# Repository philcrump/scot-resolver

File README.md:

# scot-resolver

Resolver Interface for the SCOT.

* 22-32V DC Input
* STM32F042K6 Microcontroller @ 48MHz
* MCP2562 CAN 2.0A/B Communication Interface
* AD2S1210 Resolver to Digital Converter
* AD8397 Excitation Driver
* AD8692 Receiver Amplifiers

[**Circuit Board Schematic**](https://github.com/philcrump/scot-resolver/raw/master/scot-resolver-schematic.pdf)

## PCB (CAD Render)

### June 2020 PCB Errata

* C25 has 0603 pad, C27 & C28 have 1210 pads, all should be 0805 to match the part.
* C26 has 1210 pad, should be 1206.
** Not disastrous, part still fits, with careful placement on 1210 to ensure direct contact with the pads.
* Input Voltage rating is 22-32V, not 19-36V as printed on the PCB (limited by U6-LM317 dropout and thermal).
* Optional Ripple Rejection Capacitor should be fitted across R22 (LM317 regulator)
** 2u2 50V found to prevent oscillation with hostile downstream load (oscillating U2-LT1763)
* C24 U2-LT1763 Bypass Capacitor is incorrectly placed, causes self-oscillation, and should not be populated.
** Attempt to wire this across to Vout instead as recommended also caused output oscillation when under load (25mA).
* U6-LM317 regulator gets hot, within limits but would benefit from more heatsinking / different package.

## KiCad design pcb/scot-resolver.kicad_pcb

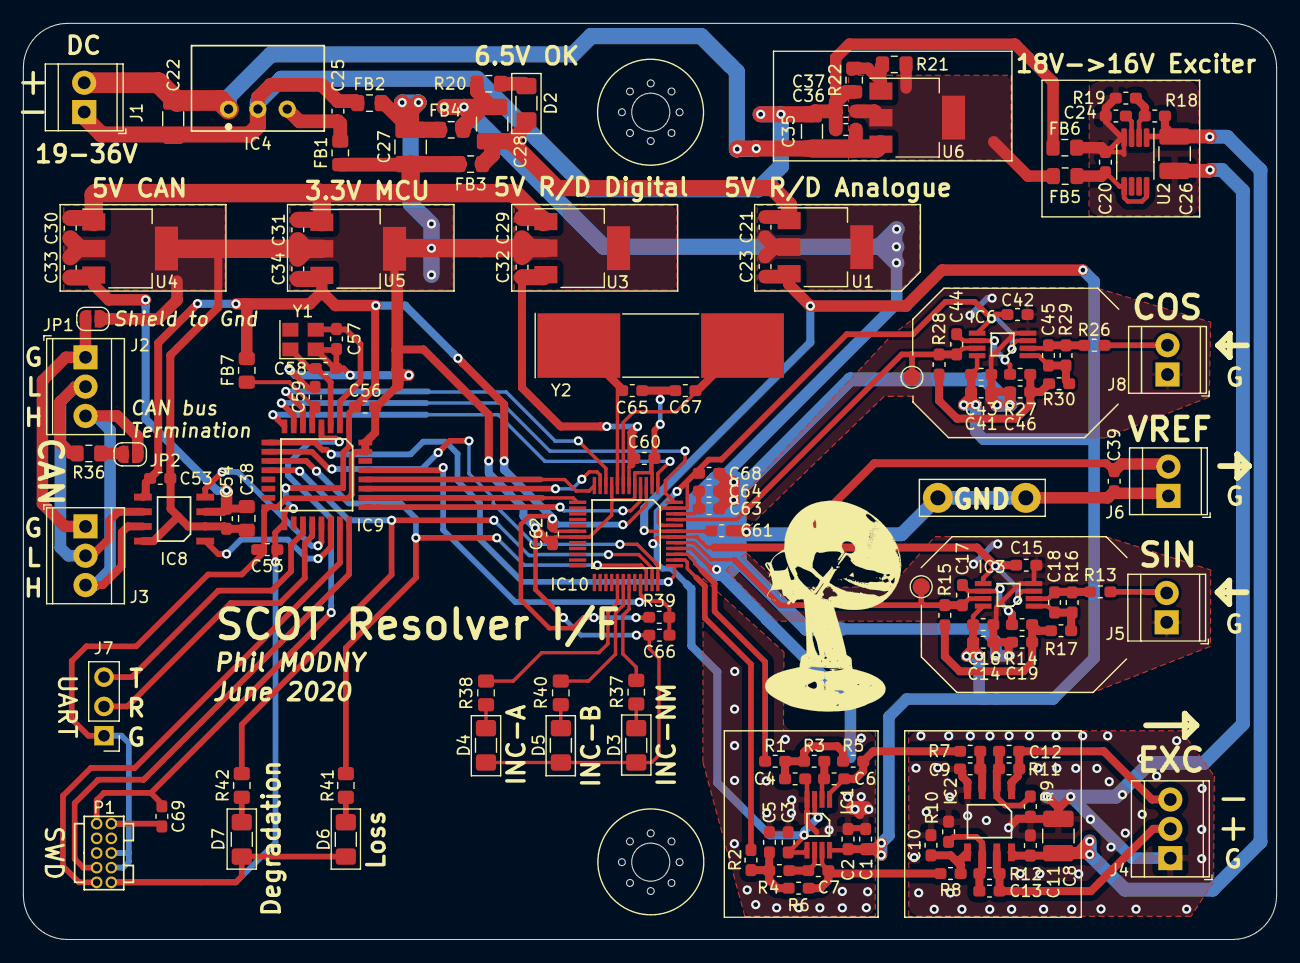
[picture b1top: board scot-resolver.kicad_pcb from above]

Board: 2 copper layers, 108.6 x 79.4 mm, 141 parts (0 on the bottom side), 83 nets.

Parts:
C1, C39, C64: 10u; C_0603_1608Metric_Pad1.05x0.95mm_HandSolder
C2, C3, C11, C15, C16, C42, C43, C55, C56, C59, C60, C61, C62, C66, C68, C69: 100n; C_0603_1608Metric_Pad1.05x0.95mm_HandSolder
C4, C5: 1n; C_0603_1608Metric_Pad1.05x0.95mm_HandSolder
C6, C7: 100p; C_0603_1608Metric_Pad1.05x0.95mm_HandSolder
C8: 10u; C_1210_3225Metric_Pad1.42x2.65mm_HandSolder
C9, C10, C12, C13: 4n7; C_0603_1608Metric_Pad1.05x0.95mm_HandSolder
C14, C20, C41: 1u; C_0603_1608Metric_Pad1.05x0.95mm_HandSolder
C17, C44: 1n2; C_0603_1608Metric_Pad1.05x0.95mm_HandSolder
C18, C45: 220p; C_0603_1608Metric_Pad1.05x0.95mm_HandSolder
C19, C46: 6n8; C_0603_1608Metric_Pad1.05x0.95mm_HandSolder
C21, C29, C30, C31: 1u/6.5V; C_0603_1608Metric_Pad1.05x0.95mm_HandSolder
C22, C35: 4u7/50V; C_1206_3216Metric_Pad1.42x1.75mm_HandSolder
C23, C32, C33: 1u/5V; C_0603_1608Metric_Pad1.05x0.95mm_HandSolder
C24: 10n/50V; C_0603_1608Metric_Pad1.05x0.95mm_HandSolder
C25: 4u7/6.5V; C_0603_1608Metric_Pad1.05x0.95mm_HandSolder
C26: 4u7/50V; C_1210_3225Metric_Pad1.42x2.65mm_HandSolder
C27, C28: 4u7/6.5V; C_1210_3225Metric_Pad1.42x2.65mm_HandSolder
C34: 1u/3.3V; C_0603_1608Metric_Pad1.05x0.95mm_HandSolder
C36: 100n/50V; C_0603_1608Metric_Pad1.05x0.95mm_HandSolder
C37: 4u7/50V; C_0603_1608Metric_Pad1.05x0.95mm_HandSolder
C38: 4u7/5V; C_0805_2012Metric_Pad1.15x1.40mm_HandSolder
C53: 100n/3V3; C_0603_1608Metric_Pad1.05x0.95mm_HandSolder
C54: 100n/5V; C_0603_1608Metric_Pad1.05x0.95mm_HandSolder
C57, C58: 8p; C_0603_1608Metric_Pad1.05x0.95mm_HandSolder
C63: 10n; C_0603_1608Metric_Pad1.05x0.95mm_HandSolder
C65, C67: 18p; C_0603_1608Metric_Pad1.05x0.95mm_HandSolder
D2, D3, D4, D5, D6, D7: LED; C_1206_3216Metric_Pad1.42x1.75mm_HandSolder
FB1, FB2, FB3, FB4, FB5, FB6: 600R@100M/1A; L_0805_2012Metric_Pad1.15x1.40mm_HandSolder
FB7: Ferrite_Bead_Small; L_0805_2012Metric_Pad1.15x1.40mm_HandSolder
H1, H2: MountingHole; M3_MOUNT
IC1, IC3, IC6: AD8692ARMZ; MSOP-8
IC2: AD8397ARZ; SOIC-8
IC4: TSR1
IC8: MCP2562; SOIC-8
IC9: STM32F0xxKxTx; LQFP-32
IC10: AD2S1210; LQFP-48
J1, J5, J6, J8: Conn_01x02_Female; TerminalBlock_TE_282834-2_1x02_P2.54mm_Horizontal
J2, J3, J4: Conn_01x03_Female; TerminalBlock_TE_282834-3_1x03_P2.54mm_Horizontal
J7: CONN_01x03; PinHeader_1x03_P2.54mm_Vertical
JP1, JP2: SolderJumper_2_Open; SolderJumper-2_P1.3mm_Open_RoundedPad1.0x1.5mm
P1: SWD; FTSH-105-01-F-D-K
R1, R2, R5, R6: 20k; R_0603_1608Metric_Pad1.05x0.95mm_HandSolder
R3, R4: 6k2; R_0603_1608Metric_Pad1.05x0.95mm_HandSolder
R7, R8: 820R; R_0603_1608Metric_Pad1.05x0.95mm_HandSolder
R9, R10: 390R; R_0603_1608Metric_Pad1.05x0.95mm_HandSolder
R11, R12: 910R; R_0603_1608Metric_Pad1.05x0.95mm_HandSolder
R13, R26: 120K; R_0603_1608Metric_Pad1.05x0.95mm_HandSolder
R14, R27: 1K2; R_0603_1608Metric_Pad1.05x0.95mm_HandSolder
R15, R28: 2K; R_0603_1608Metric_Pad1.05x0.95mm_HandSolder
R16, R29: 22K; R_0603_1608Metric_Pad1.05x0.95mm_HandSolder
R17, R30: 2K7; R_0603_1608Metric_Pad1.05x0.95mm_HandSolder
R18: 68K; R_0603_1608Metric_Pad1.05x0.95mm_HandSolder
R19: 5K6; R_0603_1608Metric_Pad1.05x0.95mm_HandSolder
R20: 1K2; R_0805_2012Metric_Pad1.15x1.40mm_HandSolder
R21: 240R/1%; R_0805_2012Metric_Pad1.15x1.40mm_HandSolder
R22: 3K2/1%; R_0805_2012Metric_Pad1.15x1.40mm_HandSolder
R36, R41, R42: 120R; R_0805_2012Metric_Pad1.15x1.40mm_HandSolder
R37, R38, R40: 67R; R_0805_2012Metric_Pad1.15x1.40mm_HandSolder
R39: 10K; R_0603_1608Metric_Pad1.05x0.95mm_HandSolder
TP1: TestPoint_Alt; TestPoint_Bridge_Pitch7.62mm_Drill1.3mm
TP3: TestPoint; TestPoint_Pad_D1.5mm
TPe: TestPoint; TestPoint_Pad_D1.5mm
U1, U3, U4: MCP1703A-5002_SOT223; SOT-223-3_TabPin2
U2: LT1762; MSOP-8_3x3mm_P0.65mm
U5: MCP1703A-3302_SOT223; SOT-223-3_TabPin2
U6: LM317_3PinPackage; SOT-223-3_TabPin2
Y1: Crystal_GND24; Crystal_SMD_Abracon_ABM8G-4Pin_3.2x2.5mm
Y2: Crystal; Crystal_SMD_SeikoEpson_MA505-2Pin_12.7x5.1mm_HandSoldering

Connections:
/CAN TXRX/3.3V_MCU: C34.1, C53.2, C55.1, C56.1, C62.1, D6.2, D7.2, FB7.2, IC8.5, IC9.1, IC9.17, IC10.3, IC10.18, P1.1, R39.1, U5.3
/CAN TXRX/5V_CAN: C33.1, C38.2, C54.2, IC8.3, U4.3
/CAN TXRX/CAN_H: IC8.7, J2.3, J3.3, JP2.2
/CAN TXRX/CAN_L: IC8.6, J2.2, J3.2, R36.2
/CAN TXRX/CAN_MCU_RXD: IC8.4, IC9.21
/CAN TXRX/CAN_MCU_TXD: IC8.1, IC9.22
/Microcontroller & Interface/5V_RESOLVER_ANALOGUE: C1.1, C2.1, C14.2, C16.2, C23.1, C41.2, C43.2, C61.1, IC1.8, IC3.8, IC6.8, IC10.43, U1.3
/Microcontroller & Interface/5V_RESOLVER_DIGITAL: C32.1, C60.1, IC10.6, U3.3
/Microcontroller & Interface/A0: IC9.9, IC10.37
/Microcontroller & Interface/A1: IC9.10, IC10.36
/Microcontroller & Interface/INC_A: IC10.29, R38.1
/Microcontroller & Interface/INC_B: IC10.30, R40.1
/Microcontroller & Interface/INC_NM: IC10.31, R37.1
/Microcontroller & Interface/RD_nRESET: C66.1, IC9.29, IC10.33, R39.2
/Microcontroller & Interface/RES0: IC9.7, IC10.48
/Microcontroller & Interface/RES1: IC9.8, IC10.1
/Microcontroller & Interface/SPI_RD_MISO: IC9.27, IC10.11
/Microcontroller & Interface/SPI_RD_MOSI: IC9.28, IC10.12
/Microcontroller & Interface/SPI_RD_SCK: IC9.26, IC10.13
/Microcontroller & Interface/SPI_RD_~CS: IC9.25, IC10.4
/Microcontroller & Interface/SWD_CLK: IC9.24, P1.4
/Microcontroller & Interface/SWD_IO: IC9.23, P1.2
/Microcontroller & Interface/UART_DEBUG_RX: IC9.20, J7.2
/Microcontroller & Interface/UART_DEBUG_TX: IC9.19, J7.3
/Microcontroller & Interface/~DOT: IC9.12, IC10.35, R42.2
/Microcontroller & Interface/~LOT: IC9.11, IC10.34, R41.2
/Microcontroller & Interface/~SAMPLE: IC9.6, IC10.10
/Power Supplies/0V_EXCITER: C8.2, C9.2, C10.1, C11.2, C20.2, C24.2, C26.2, FB6.2, IC2.4, J4.1, R9.1, R10.2, R19.2, U2.4
/Power Supplies/ANALOG_6.5V+: C21.1, C28.1, D2.2, FB3.2, U1.1
/Power Supplies/DIGITAL_6.5V+: C27.1, C29.1, C30.1, C31.1, FB1.1, FB3.1, U3.1, U4.1, U5.1
/Power Supplies/EXCITER_16V+: C8.1, C11.1, C26.1, IC2.8, R18.1, U2.1
/Power Supplies/POWER_28V+: C22.1, C35.1, C36.1, IC4.1, J1.2, U6.3
/Power Supplies/POWER_28V-: C22.2, C25.2, C35.2, C36.2, C37.2, FB2.1, FB6.1, IC4.2, J1.1, R22.2
/Resolver Exciter/AD2S1210_EXC+: IC10.38, R2.1
/Resolver Exciter/AD2S1210_EXC-: IC10.39, R1.2
/Resolver Exciter/AD2S1210_VREF: C3.1, C15.2, C39.1, C42.2, C68.1, IC1.3, IC1.5, IC3.3, IC3.5, IC6.3, IC6.5, IC10.42, IC10.44, IC10.47, J6.2
/Resolver Exciter/EXC+_OUTPUT: C13.1, IC2.7, J4.2, R12.1
/Resolver Exciter/EXC-_OUTPUT: C12.2, IC2.1, J4.3, R11.2
/Resolver Receiver COS+/AD2S1210_INPUT: C44.2, IC6.7, IC10.45, R28.1, TP3.1
/Resolver Receiver COS+/RECEIVER_INPUT: J8.2, R26.1
/Resolver Receiver SIN+/AD2S1210_INPUT: C17.2, IC3.7, IC10.41, R15.1, TPe.1
/Resolver Receiver SIN+/RECEIVER_INPUT: J5.2, R13.1
GND: C27.2, C29.2, C30.2, C31.2, C32.2, C33.2, C34.2, C38.1, C53.1, C54.1, C55.2, C56.2, C57.1, C58.2, C59.2, C60.2, C62.2, C65.2, C66.2, C67.2, C69.2, D3.1, D4.1, D5.1, FB2.2, FB4.1, IC8.2, IC8.8, IC9.16, IC9.31, IC9.32, IC10.2, IC10.5, IC10.9, IC10.19, J7.1, JP1.2, P1.3, P1.5, P1.9, U3.2, U4.2, U5.2, Y1.2
GNDA: C1.2, C2.2, C3.2, C4.2, C5.1, C14.1, C15.1, C16.1, C19.2, C21.2, C23.2, C28.2, C39.2, C41.1, C42.1, C43.1, C46.2, C61.2, C63.2, C64.2, C68.2, FB4.2, IC1.4, IC3.4, IC6.4, IC10.40, J5.1, J6.1, J8.1, R20.2, TP1.1, U1.2
unnamed: C4.1, R1.1, R3.2, R5.2
unnamed: C5.2, R2.2, R4.1, R6.1
unnamed: C6.1, IC1.1, R5.1, R7.2
unnamed: C6.2, IC1.2, R3.1
unnamed: C7.1, IC1.6, R4.2
unnamed: C7.2, IC1.7, R6.2, R8.2
unnamed: C9.1, IC2.3, R7.1
unnamed: C10.2, IC2.5, R8.1
unnamed: C12.1, IC2.2, R9.2, R11.1
unnamed: C13.2, IC2.6, R10.1, R12.2
unnamed: C17.1, IC3.6, R14.1
unnamed: C18.1, IC3.2, R13.2, R16.1
unnamed: C18.2, IC3.1, R16.2, R17.2
unnamed: C19.1, R14.2, R15.2, R17.1
unnamed: C20.1, FB5.2, U2.5, U2.8
unnamed: C24.1, U2.3
unnamed: C25.1, FB1.2, IC4.3
unnamed: C37.1, FB5.1, R21.1, U6.2
unnamed: C44.1, IC6.6, R27.1
unnamed: C45.1, IC6.2, R26.2, R29.1
unnamed: C45.2, IC6.1, R29.2, R30.2
unnamed: C46.1, R27.2, R28.2, R30.1
unnamed: C57.2, IC9.2, Y1.3
unnamed: C58.1, IC9.3, Y1.1
unnamed: C59.1, FB7.1, IC9.5
unnamed: C63.1, C64.1, IC10.46
unnamed: C65.1, IC10.8, Y2.1
unnamed: C67.1, IC10.7, Y2.2
unnamed: C69.1, IC9.4, P1.10
unnamed: D2.1, R20.1
unnamed: D3.2, R37.2
unnamed: D4.2, R38.2
unnamed: D5.2, R40.2
unnamed: D6.1, R41.1
unnamed: D7.1, R42.1
unnamed: J2.1, J3.1, JP1.1
unnamed: JP2.1, R36.1
unnamed: R18.2, R19.1, U2.2
unnamed: R21.2, R22.1, U6.1

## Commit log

2019-12-28 Update pcb/lib/agg-kicad ref.
2019-12-28 Initial commit of files.
2019-12-28 Add LICENSE
2019-12-29 Add README.md
2020-01-01 WIP PCB (starting layout)
2020-01-01 Add datasheets.
2020-01-05 PCB Progress, laying tracks.
2020-01-06 sym-lib-table: Use relative path for agg-kicad lib.
2020-01-06 Progress.
2020-02-07 WIP.
2020-02-17 WIP (nearly there!)
2020-02-19 WIP..
2020-02-19 Sent to fab (fab5)
2020-02-19 Renaming of files.
2020-03-03 pcb: Add labels and values to schematic.
2020-03-03 Add BOM.
2020-03-05 pcb/BOM: Add mosuer parts list.
2020-03-06 pcb/BOM: Add warning of mistake (2nd can txrx ordered not a diode)
2020-03-29 Add initial firmware.
2020-03-29 pcb/agg-kicad: Update lib reference.
2020-04-01 Flesh out firmware.
2020-04-01 Add STM32F0 ref manual to docs.
2020-04-02 Firmware tweaks.
2020-04-02 Add crude python canbus view script.
2020-04-03 firmware/tools/can_view.py
2020-04-04 firmware: Fix git version in CAN sysinfo messages.
2020-04-04 pcb/lib/agg-kicad: Change to https URL for Travis CI compatibility.
2020-04-04 firmware/build: Fix werror default.
2020-04-04 firmware: Add CAN RX filter.
2020-04-05 firmware/ChibiOS: Update ref.
2020-04-05 firmware: CAN tweaks.
2020-04-06 firmware: Add reset of RD IC on _init() and on config parity error.
2020-04-10 firmware: Build tweaks.
2020-04-10 pcb/: Re-render schematic pdf.
2020-04-10 firmware/ad2s1210c: Re-order RD start up sequence to fix reported faults.
2020-04-11 firmware: Re-enable System Info CAN messages.
2020-04-20 WIP PCB v2.
2020-04-25 pcb: V2 schematic updates (PCB still to do).
2020-04-26 pcb: Add Receiver second stage calculations to schematic.
2020-04-26 pcb: Add 10u to VREF, all 0402->0603
2020-04-26 pcb: Add analog testpoints.
2020-04-26 pcb: WIP layout of v2.
2020-05-03 firmware/ChibiOS: Update ref to latest 20.3.x
2020-05-03 firmware: Just one packet type for position, with mandatory fault byte.
2020-05-03 firmware/build: Add multithread build option.
2020-05-03 .travis.yml: Use multithread build in CI.
2020-05-31 firmware/Chibi: Update ref.
2020-05-31 travis: Update to 2020 Q2 compiler.
2020-05-31 firmware/cfg/halconf: Disable CAN sleep mode.
2020-06-02 pcb: Progress on v2 layout.
2020-06-02 pcb: Clear up exciter ground rail (sch & pcb).
2020-06-03 pcb: Progress on layout.
2020-06-04 pcb: Finish v2 and send off for manufacture.
2020-06-05 pcb: Add v2 BOM, fix some component values.
2020-06-05 pcb/BOM: Add quickpaste list.
2020-06-05 pcb/BOM: De-duplicate BOM lines.
2020-06-08 firmware/Makefile: Enable GCC version check now Chibi bug #985 fixed.
2020-06-09 firmware/can.c: Use native 16b slots.
2020-06-12 firmware/can.c: Fix 32b gitversion.
2020-06-22 firmware/Makefile: Use auto FPU for cpu.
2020-06-22 pcb/BOM: Fixes (unfinished).
2020-07-25 firmware/: Load CAN address from STM32 config id. Add STM32 ID for existing board.
2020-08-09 pcb/BOM: Minor updates.
2020-08-15 pcb/BOM: Checked C8 footprint - is 1210.
2020-08-16 firmware/flash: Add Device ID readout. (`./flash -I`)
2020-08-16 firmware/config.c: Add STM32 ID for new Azimuth resolver board (June 2020)
2020-08-16 README: Add June 2020 PCB errata.
2020-08-18 README: Expand PCB errata.
2020-08-29 Add more PCB errata notes.
2020-08-29 firmware/flash: Add C-friendly STM32 ID output.
2020-08-29 firmware/config.c: Swap EL resolver board for June2020 board.
